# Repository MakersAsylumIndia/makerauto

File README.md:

# makerauto
blinky badge for the Maker Auto

***FEATURES***

1. Three LED's with series current limit resistors
2. One CR2032 Coin Battery
3. Use either One, Two or Three LEDs.
4. Use Red, Green and Blue LEDs, or all White LEDs or whatever you choose
5. Use a Blinking LED
6. Replace Resistor with LDR to have light controlled brightness

***LEARN***

1. How to Solder
2. Resistor Color Code
3. Use of Multimeter to check LED, Resistor and Battery

DISCUSSION FORUM : http://discuss.makersasylum.com/t/maker-auto-rickshaw/55/36

rev1 renders

License
-------
[CERN Open Hardware Licence v1.2 ]

[CERN Open Hardware Licence v1.2 ]:http://www.ohwr.org/attachments/2388/cern_ohl_v_1_2.txt

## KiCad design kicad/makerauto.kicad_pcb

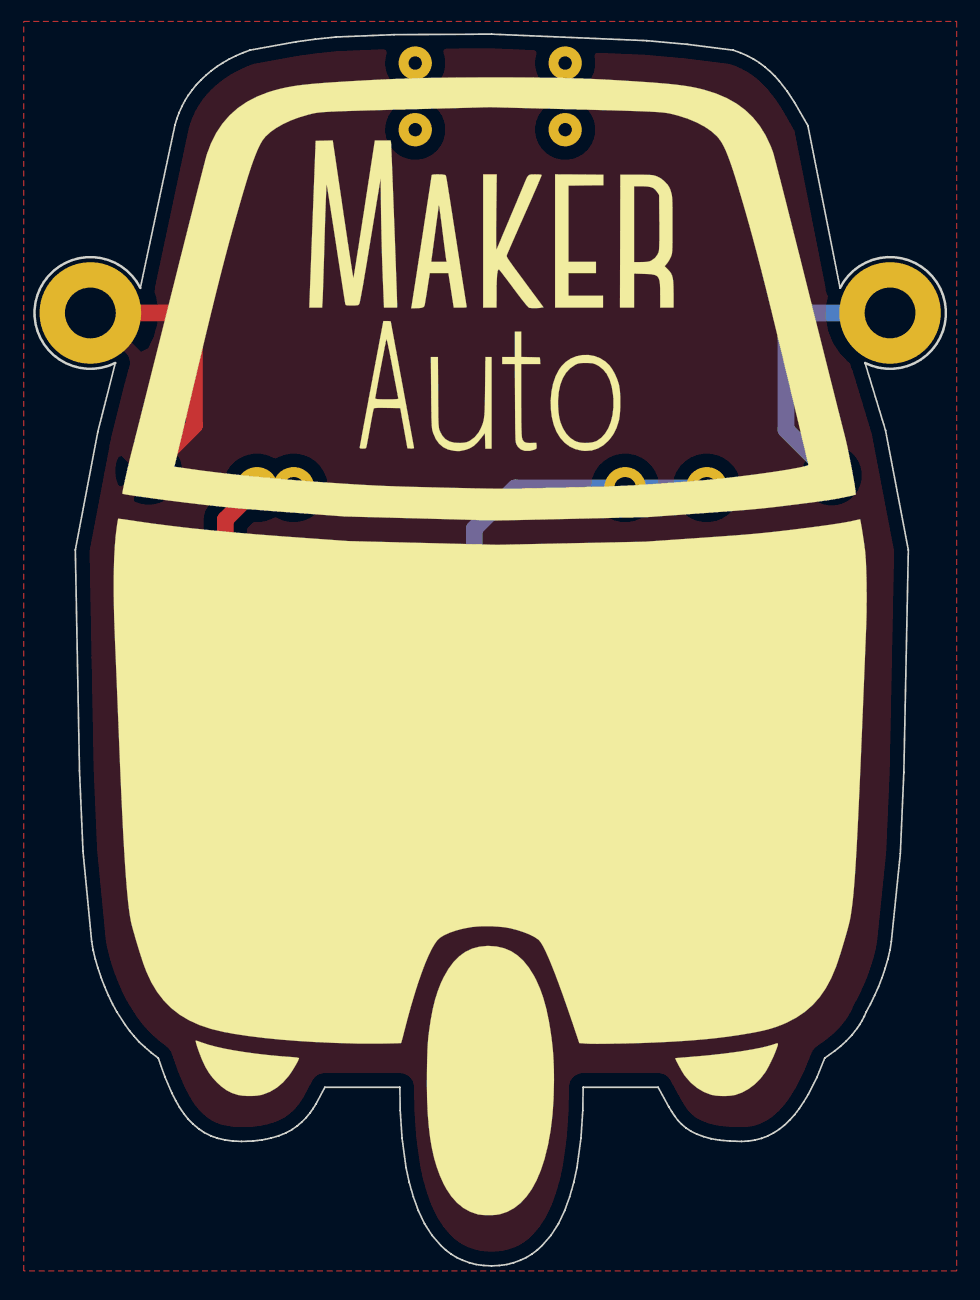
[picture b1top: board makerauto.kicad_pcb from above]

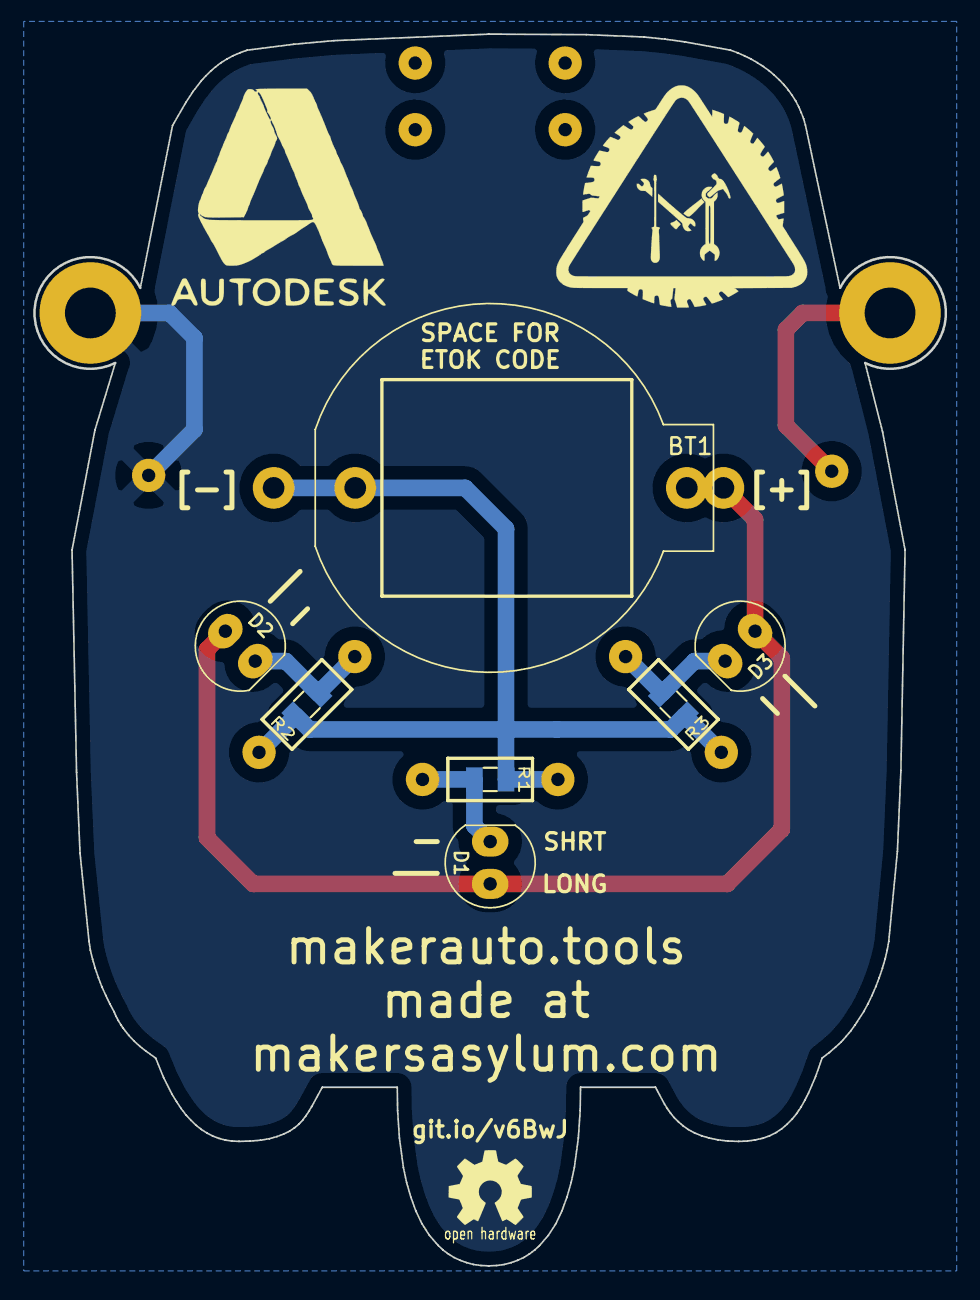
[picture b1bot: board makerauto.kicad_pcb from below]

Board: 2 copper layers, 54.7 x 73.9 mm, 17 parts (5 on the bottom side), 7 nets.

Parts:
BT1: BATT_HOLDER; cr2032_02
D1: Red; LED-5MM
D2: Grn; LED-5MM
D3: Blu; LED-5MM
LOGO1: OPEN_HARDWARE_1; Logo_silk_OSHW_6x6mm
P1: Logo_MA; ma_logo
P2, P3: Mirror; MTG_3mm
P4, P5, P6, P7, P8, P9: Pin; MTG_0mm8
R1, R2, R3: 47E; r_0805

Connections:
/3V: BT1.1, D1.1, D2.1, D3.1
/BOT: P3.1, P9.1
/GND: BT1.2, R1.1, R2.1, R3.1
/LED_blu: D3.2, R3.2
/LED_grn: D2.2, R2.2
/LED_red: D1.2, R1.2
/TOP: P2.1, P8.1

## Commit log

2016-08-11 initial layout for Maker Auto blinky badge. Outline defined
2016-08-11 initial layout
2016-08-11 gerbers and pdf's generated
2016-08-11 added logos
2016-08-12 added copper fill zones
2016-08-13 edited back silk legend
2016-08-13 complete. final gerbers generated
